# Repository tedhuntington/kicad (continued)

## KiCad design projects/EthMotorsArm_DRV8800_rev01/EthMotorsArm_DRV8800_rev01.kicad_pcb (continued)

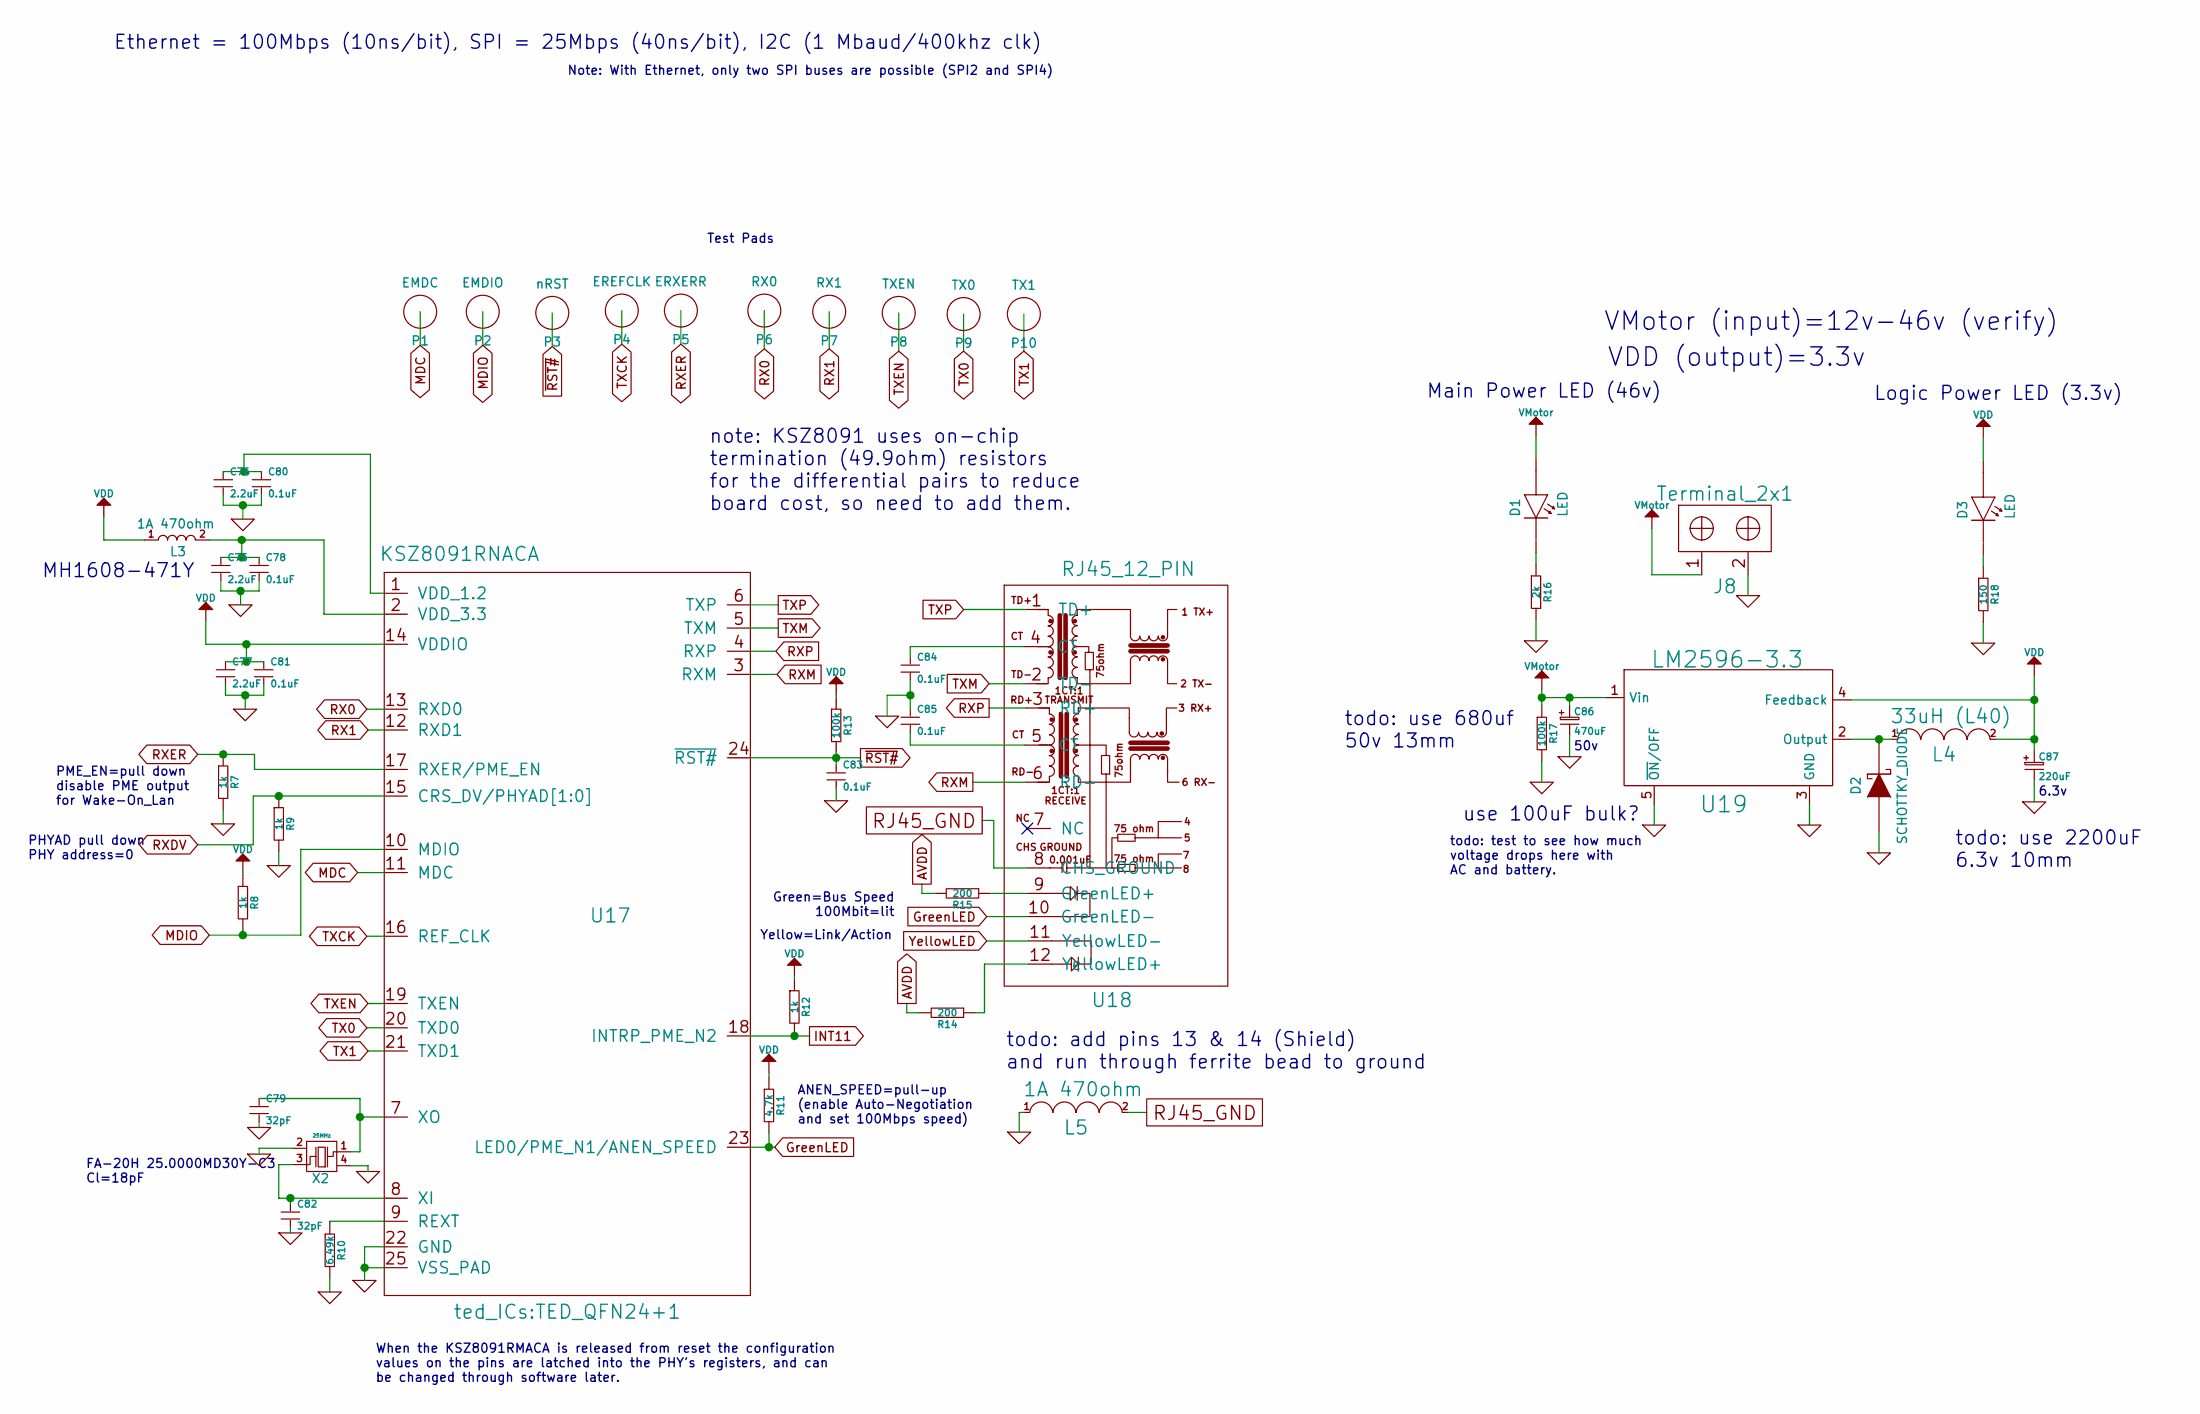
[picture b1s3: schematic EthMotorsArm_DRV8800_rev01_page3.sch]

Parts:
C75, C76, C77: 2.2uF; TED_SM0603_C
C78, C80, C81, C83, C84, C85: 0.1uF; TED_SM0603_C
C79, C82: 32pF; TED_SM0603_C
C86: 470uF; CP_Radial_D12.5mm_P5.00mm
C87: 220uF; TED_c_elec_radial_10mm
D1, D3: LED; TED_SM1206_LED
D2: SCHOTTKY_DIODE; TED_DO-214AC
J8: Terminal_2x1; TED_TERMINAL_5mm_2x1
L3, L5: 1A 470ohm; TED_SM0603_R
L4: 33uH (L40); INDUCTOR_12x12_SMD
P1: EMDC; TED_TEST_PAD
P2: EMDIO; TED_TEST_PAD
P3: nRST; TED_TEST_PAD
P4: EREFCLK; TED_TEST_PAD
P5: ERXERR; TED_TEST_PAD
P6: RX0; TED_TEST_PAD
P7: RX1; TED_TEST_PAD
P8: TXEN; TED_TEST_PAD
P9: TX0; TED_TEST_PAD
P10: TX1; TED_TEST_PAD
R7, R8, R9, R12: 1k; TED_SM0603_R
R10: 6.49k; TED_SM0603_R
R11: 4.7k; TED_SM0603_R
R13, R17: 100k; TED_SM0603_R
R14, R15: 200; TED_SM0603_R
R16: 2k; TED_SM0603_R
R18: 150; TED_SM0603_R
U17: KSZ8091RNACA; TED_QFN24+1
U18: RJ45_12_PIN; TED_RJ45_12pin
U19: LM2596-3.3; TED_TO263
X2: 25MHz; TED_crystal_FA-20H

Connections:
AVDD: R14.2, R15.2
GND: C75.2, C76.2, C77.2, C78.2, C79.2, C80.2, C81.2, C82.2, C83.2, C84.2, C85.1, C86.2, C87.2, D2.2 (A), J8.2, L5.1, R7.2, R9.2, R10.2, R16.2, R17.2, R18.2, U17.22 (GND), U17.25 (VSS_PAD), U19.3 (GND), U19.5 (~ON~/OFF), X2.2, X2.4; also elsewhere on the board
GreenLED: R11.2, U17.23 (LED0/PME_N1/ANEN_SPEED), U18.10 (GreenLED-)
INT11: R12.2, U17.18 (INTRP_PME_N2); also elsewhere on the board
MDC: P1.1, U17.11 (MDC); also elsewhere on the board
MDIO: P2.1, R8.2, U17.10 (MDIO); also elsewhere on the board
unnamed: C75.1, C78.1, L3.2, U17.2 (VDD_3.3)
unnamed: C76.1, C80.1, U17.1 (VDD_1.2)
unnamed: C79.1, U17.7 (XO), X2.1
unnamed: C82.1, U17.8 (XI), X2.3
unnamed: C84.1, U18.4 (CT)
unnamed: C85.2, U18.5 (CT)
unnamed: D1.2 (K), R16.1
unnamed: D2.1 (K), L4.1, U19.2 (Output)
unnamed: D3.2 (K), R18.1
unnamed: R10.1, U17.9 (REXT)
unnamed: R14.1, U18.12 (YellowLED+)
unnamed: R15.1, U18.9 (GreenLED+)
RJ45_GND: L5.2, U18.8 (CHS_GROUND)
RX0: P6.1, U17.13 (RXD0); also elsewhere on the board
RX1: P7.1, U17.12 (RXD1); also elsewhere on the board
RXDV: R9.1, U17.15 (CRS_DV/PHYAD[1:0]); also elsewhere on the board
RXER: P5.1, R7.1, U17.17 (RXER/PME_EN); also elsewhere on the board
RXM: U17.3 (RXM), U18.6 (RD-)
RXP: U17.4 (RXP), U18.3 (RD+)
TX0: P9.1, U17.20 (TXD0); also elsewhere on the board
TX1: P10.1, U17.21 (TXD1); also elsewhere on the board
TXCK: P4.1, U17.16 (REF_CLK); also elsewhere on the board
TXEN: P8.1, U17.19 (TXEN); also elsewhere on the board
TXM: U17.5 (TXM), U18.2 (TD-)
TXP: U17.6 (TXP), U18.1 (TD+)
VDD: C77.1, C81.1, C87.1, D3.1 (A), L3.1, L4.2, R8.1, R11.1, R12.1, R13.1, U17.14 (VDDIO), U19.4 (Feedback); also elsewhere on the board
VMotor: C86.1, D1.1 (A), J8.1, R17.1, U19.1 (Vin); also elsewhere on the board
YellowLED: U18.11 (YellowLED-); also elsewhere on the board
~RST#~: C83.1, P3.1, R13.2, U17.24 (~RST#~)

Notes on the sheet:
Ethernet = 100Mbps (10ns/bit), SPI = 25Mbps (40ns/bit), I2C (1 Mbaud/400khz clk)
Note: With Ethernet, only two SPI buses are possible (SPI2 and SPI4)
Yellow=Link/Action
Green=Bus Speed 100Mbit=lit
VDD (output)=3.3v
VMotor (input)=12v-46v (verify)
50v
6.3v
Main Power LED (46v)
Logic Power LED (3.3v)
note: KSZ8091 uses on-chip termination (49.9ohm) resistors for the differential pairs to reduce board cost, so need to add them.
MH1608-471Y
FA-20H 25.0000MD30Y-C3 Cl=18pF
ANEN_SPEED=pull-up (enable Auto-Negotiation and set 100Mbps speed)
PME_EN=pull down disable PME output for Wake-On_Lan
PHYAD pull down PHY address=0
When the KSZ8091RMACA is released from reset the configuration values on the pins are latched into the PHY's registers, and can be changed through software later.
Test Pads
todo: add pins 13 & 14 (Shield) and run through ferrite bead to ground
todo: test to see how much voltage drops here with AC and battery.
use 100uF bulk?
todo: use 680uf 50v 13mm
todo: use 2200uF 6.3v 10mm

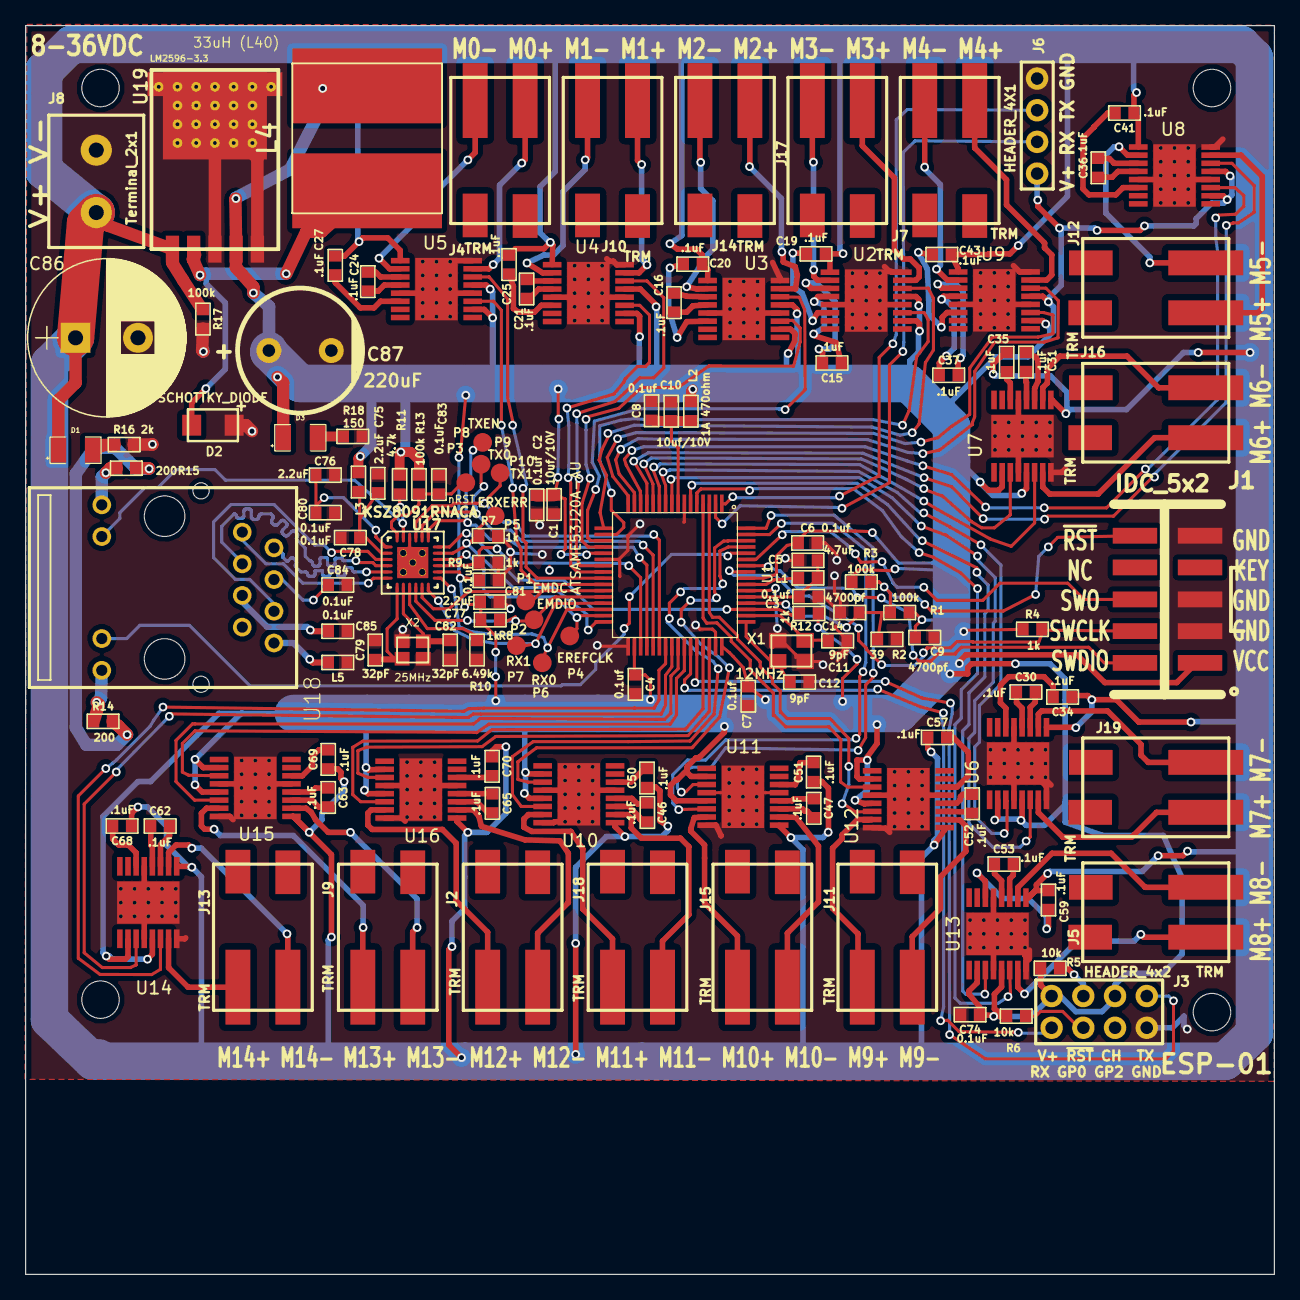
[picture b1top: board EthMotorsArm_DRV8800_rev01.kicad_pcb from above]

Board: 2 copper layers, 100.0 x 100.0 mm, 137 parts (0 on the bottom side), 155 nets.

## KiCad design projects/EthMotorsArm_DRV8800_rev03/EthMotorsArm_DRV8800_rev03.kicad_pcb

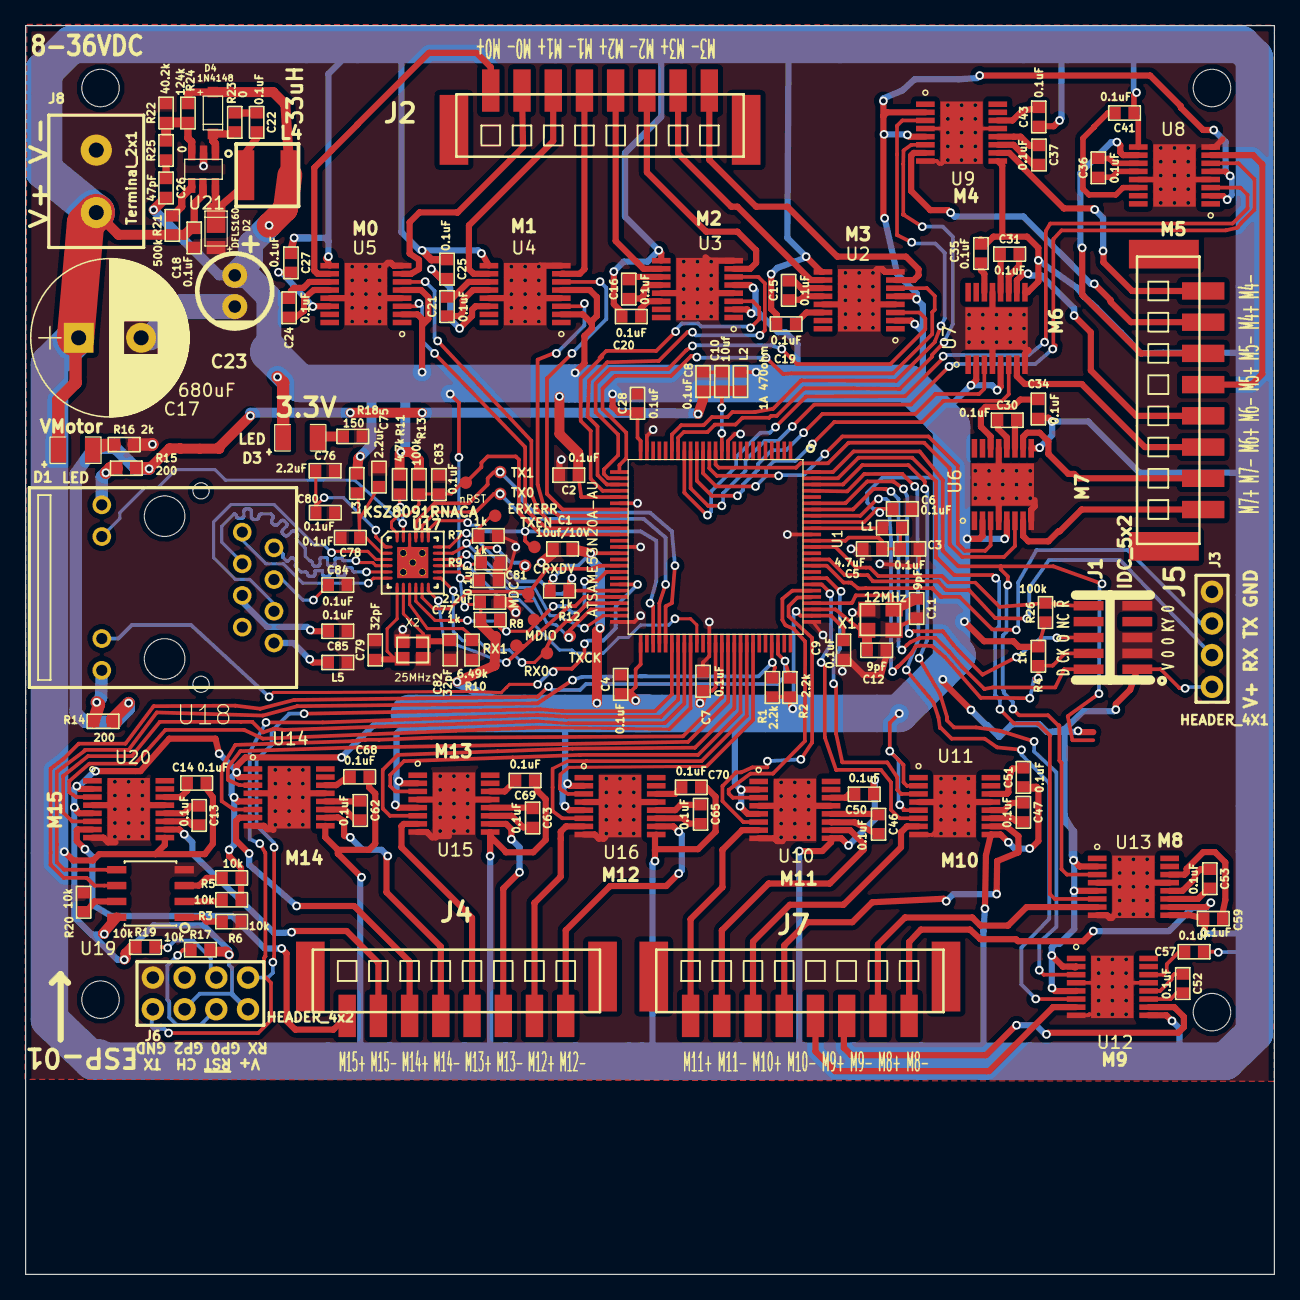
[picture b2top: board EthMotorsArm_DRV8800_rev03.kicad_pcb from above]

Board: 2 copper layers, 100.0 x 100.0 mm, 142 parts (0 on the bottom side), 172 nets.

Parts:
C1: 10uf/10V; TED_SM1608_0603_C
C2, C3, C4, C6, C7, C8, C9, C13, C14, C15, C16, C18, C19, C20, C21, C22, C24, C25, C27, C28, C30, C31, C34, C35, C36, C37, C41, C43, C46, C47, C50, C51, C52, C53, C57, C59, C62, C63, C65, C68, C69, C70, C78, C80, C81, C83, C84, C85: 0.1uF; TED_SM1608_0603_C
C5: 4.7uF; TED_SM1608_0603_C
C10: 10uf; TED_SM1608_0603_C
C11, C12: 9pF; TED_SM1608_0603_C
C17: 680uF; CP_Radial_D12.5mm_P5.00mm
C23: 220uF; TED_c_elec_radial_6.3mm
C26: 47pF; TED_SM1608_0603_C
C75, C76, C77: 2.2uF; TED_SM1608_0603_C
C79, C82: 32pF; TED_SM1608_0603_C
D1, D3: LED; TED_SM1206_LED
D2: DFLS160; TED_PowerDI123
D4: 1N4148; TED_SOD-123
H1, H2, H3, H4: HOLE; TED_Hole_3mm
J1: IDC_5x2; TED_IDC_5x2_1.27pitch_SMD_nm
J2, J4, J5, J7: Terminal_8x1_rev; TED_Terminal_8x1_1814760
J3: HEADER_4X1; TED_HEADER_4x1
J6: HEADER_4x2; TED_HEADER_4x2
J8: Terminal_2x1; TED_TERMINAL_5mm_2x1
L1, L2, L3, L5: 1A 470ohm; TED_SM0603_R
L4: 33uH; INDUCTOR_5x5_SMD
P1: MDC; TED_TEST_PAD
P2: MDIO; TED_TEST_PAD
P3: nRST; TED_TEST_PAD
P4: TXCK; TED_TEST_PAD
P5: ERXERR; TED_TEST_PAD
P6: RX0; TED_TEST_PAD
P7: RX1; TED_TEST_PAD
P8: TXEN; TED_TEST_PAD
P9: TX0; TED_TEST_PAD
P10: TX1; TED_TEST_PAD
P11: CRXDV; TED_TEST_PAD
R1, R2: 2.2k; TED_SM0603_R
R3, R5, R6, R17, R19, R20: 10k; TED_SM0603_R
R4, R7, R8, R9, R12: 1k; TED_SM0603_R
R10: 6.49k; TED_SM0603_R
R11: 4.7k; TED_SM0603_R
R13, R26: 100k; TED_SM0603_R
R14, R15: 200; TED_SM0603_R
R16: 2k; TED_SM0603_R
R18: 150; TED_SM0603_R
R21: 500k; TED_SM0603_R
R22: 40.2k; TED_SM0603_R
R23, R25: 0; TED_SM0603_R
R24: 124k; TED_SM0603_R
U1: ATSAME53N20A-AU; TED_TQFP100
U2, U3, U4, U5, U6, U7, U8, U9, U10, U11, U12, U13, U14, U15, U16, U20: DRV8800_PWP; TSSOP_16+1H
U17: KSZ8091RNACA; TED_QFN24+1
U18: RJ45_12_PIN; TED_RJ45_12pin
U19: AT24MAC402; SOIC-8
U21: MP2456; TSOT23-6
X1: 12MHz; crystal_3.2_2.5
X2: 25MHz; TED_crystal_FA-20H

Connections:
CRXDV: P11.1, R9.1, U1.60, U17.15
ESP_RX_SAM_TX: J6.8, U1.56
ESP_TX_SAM_RX: J6.1, U1.57
GND: C1.2, C2.2, C3.2, C4.2, C5.2, C6.2, C7.2, C8.2, C9.2, C10.2, C11.2, C12.2, C17.2, C18.2, C23.2, C28.2, C75.2, C76.2, C77.2, C78.2, C79.2, C80.2, C81.2, C82.2, C83.2, C84.2, C85.1, D2.1, J1.3, J1.5, J1.9, J3.4, J6.2, J8.2, L5.1, R3.2, R7.2, R9.2, R10.2, R16.2, R18.2, R20.1, R22.2, U1.11, U1.24, U1.31, U1.38, U1.50, U1.62, U1.76, U1.90, U2.4, U2.8, U2.13, U2.17, U3.4, U3.8, U3.13, U3.17, U4.4, U4.8, U4.13, U4.17, U5.4, U5.8, U5.13, U5.17, U6.4, U6.8, U6.13, U6.17, U7.4, U7.8, U7.13, U7.17, U8.4, U8.8, U8.13, U8.17, U9.4, U9.8, U9.13, U9.17, U10.4, U10.8, U10.13, U10.17, U11.4, U11.8, U11.13, U11.17, U12.4, U12.8, U12.13, U12.17, U13.4, U13.8, U13.13, U13.17, U14.4, U14.8, U14.13, U14.17, U15.4, U15.8, U15.13, U15.17, U16.4, U16.8, U16.13, U16.17, U17.22, U17.25, U19.4, U20.4, U20.8, U20.13, U20.17, U21.2, X1.2, X1.4, X2.2, X2.4
GreenLED: R11.2, U17.23, U18.10
INT15: R12.2, U1.45, U17.18
M0+: J2.2, U5.7
M0-: J2.1, U5.10
M0_1_PB12: U1.34, U5.6
M0_2_PB13: U1.35, U5.3
M1+: J2.4, U4.7
M1-: J2.3, U4.10
M1_1_PB10: U1.32, U4.6
M1_2_PB11: U1.33, U4.3
M2+: J2.6, U3.7
M2-: J2.5, U3.10
M2_1_PA10: U1.28, U3.6
M2_2_PA11: U1.29, U3.3
M3+: J2.8, U2.7
M3-: J2.7, U2.10
M3_1_PA08: U1.26, U2.6
M3_2_PA09: U1.27, U2.3
M4+: J5.2, U9.7
M4-: J5.1, U9.10
M4_1_PA06: U1.19, U9.6
M4_2_PA07: U1.20, U9.3
M5+: J5.4, U8.7
M5-: J5.3, U8.10
M5_1_PA04: U1.17, U8.6
M5_2_PA05: U1.18, U8.3
M6+: J5.6, U7.7
M6-: J5.5, U7.10
M6_1_PB08: U1.15, U7.6
M6_2_PB09: U1.16, U7.3
M7+: J5.8, U6.7
M7-: J5.7, U6.10
M7_1_PB06: U1.13, U6.6
M7_2_PB07: U1.14, U6.3
M8+: J7.2, U13.7
M8-: J7.1, U13.10
M8_1_PB02: U1.99, U13.6
M8_2_PB03: U1.100, U13.3
M9+: J7.4, U12.7
M9-: J7.3, U12.10
M9_1_PB00: U1.97, U12.6
M9_2_PB01: U1.98, U12.3
M10+: J7.6, U11.7
M10-: J7.5, U11.10
M10_1_PC24: U1.82, U11.6
M10_2_PC25: U1.83, U11.3
M11+: J7.8, U10.7
M11-: J7.7, U10.10
M11_1_PB24: U1.80, U10.6
M11_2_PB25: U1.81, U10.3
M12+: J4.2, U16.7
M12-: J4.1, U16.10
M12_1_PA24: U1.68, U16.6
M12_2_PA25: U1.69, U16.3
M13+: J4.4, U15.7
M13-: J4.3, U15.10
M13_1_PA22: U1.66, U15.6
M13_2_PA23: U1.67, U15.3
M14+: J4.6, U14.7
M14-: J4.5, U14.10
M14_1_PA20: U1.64, U14.6
M14_2_PA21: U1.65, U14.3
M15+: J4.8, U20.7
M15-: J4.7, U20.10
M15_1_PB20: U1.58, U20.6
M15_2_PB21: U1.59, U20.3
MDC: P1.1, U1.41, U17.11
MDIO: P2.1, R8.2, U1.42, U17.10
unnamed: C13.1, U20.12
unnamed: C13.2, U20.11
unnamed: C14.2, U20.14
unnamed: C15.1, U2.12
unnamed: C15.2, U2.11
unnamed: C16.1, U3.12
unnamed: C16.2, U3.11
unnamed: C19.2, U2.14
unnamed: C20.2, U3.14
unnamed: C21.1, U4.12
unnamed: C21.2, U4.11
unnamed: C22.1, R23.2
unnamed: C22.2, D2.2, L4.1, U21.6
unnamed: C24.1, U5.12
unnamed: C24.2, U5.11
unnamed: C25.2, U4.14
unnamed: C26.1, R25.1
unnamed: C27.2, U5.14
unnamed: C30.1, U6.12
unnamed: C30.2, U6.11
unnamed: C31.1, U7.12
unnamed: C31.2, U7.11
unnamed: C34.2, U6.14
unnamed: C35.2, U7.14
unnamed: C36.1, U8.12
unnamed: C36.2, U8.11
unnamed: C37.1, U9.12
unnamed: C37.2, U9.11
unnamed: C41.2, U8.14
unnamed: C43.2, U9.14
unnamed: C46.1, U10.12
unnamed: C46.2, U10.11
unnamed: C47.1, U11.12
unnamed: C47.2, U11.11
unnamed: C50.2, U10.14
unnamed: C51.2, U11.14
unnamed: C52.1, U12.12
unnamed: C52.2, U12.11
unnamed: C53.1, U13.12
unnamed: C53.2, U13.11
unnamed: C57.2, U12.14
unnamed: C59.2, U13.14
unnamed: C62.1, U14.12
unnamed: C62.2, U14.11
unnamed: C63.1, U15.12
unnamed: C63.2, U15.11
unnamed: C65.1, U16.12
unnamed: C65.2, U16.11
unnamed: C68.2, U14.14
unnamed: C69.2, U15.14
unnamed: C70.2, U16.14
unnamed: C75.1, C78.1, L3.2, U17.2
unnamed: C76.1, C80.1, U17.1
unnamed: C79.1, U17.7, X2.1
unnamed: C82.1, U17.8, X2.3
unnamed: C84.1, U18.4
unnamed: C85.2, U18.5
unnamed: D1.2, R16.1
unnamed: D3.2, R18.1
unnamed: D4.2, R23.1, U21.1
unnamed: J6.5, R17.1
unnamed: J6.6, R19.2
unnamed: R3.1, U19.1
unnamed: R5.1, U19.3
unnamed: R6.1, U19.2
unnamed: R10.1, U17.9
unnamed: R14.1, U18.12
unnamed: R15.1, U18.9
unnamed: R20.2, U19.7
unnamed: R21.2, U21.4
unnamed: R22.1, R24.2, R25.2, U21.3
RJ45_GND: L5.2, U18.8
RX0: P6.1, U1.47, U17.13
RX1: P7.1, U1.46, U17.12
RXER: P5.1, R7.1, U1.49, U17.17
RXM: U17.3, U18.6
RXP: U17.4, U18.3
SCL: R2.1, U1.73, U19.6
SDA: R1.1, U1.72, U19.5
SWCLK: J1.4, R4.2, U1.93
SWDIO: J1.2, U1.94
SWO: J1.6, U1.95
TX0: P9.1, U1.54, U17.20
TX1: P10.1, U1.55, U17.21
TXCK: P4.1, U1.48, U17.16
TXEN: P8.1, U1.53, U17.19
TXM: U17.5, U18.2
TXP: U17.6, U18.1
USART1RX: J3.2, U1.86
USART1TX: J3.3, U1.85
VDDANA: C8.1, C10.1, L2.2, R14.2, R15.2, U1.12
VDDIO: C1.1, C2.1, C4.1, C6.1, C7.1, C9.1, C23.1, C26.2, C28.1, C77.1, C81.1, D3.1, D4.1, J1.1, J3.1, J6.3, J6.7, L2.1, L3.1, L4.2, R1.2, R2.2, R4.1, R5.2, R6.2, R8.1, R11.1, R12.1, R13.1, R17.2, R19.1, R24.1, R26.1, U1.25, U1.30, U1.39, U1.51, U1.63, U1.77, U1.92, U2.2, U2.5, U3.2, U3.5, U4.2, U4.5, U5.2, U5.5, U6.2, U6.5, U7.2, U7.5, U8.2, U8.5, U9.2, U9.5, U10.2, U10.5, U11.2, U11.5, U12.2, U12.5, U13.2, U13.5, U14.2, U14.5, U15.2, U15.5, U16.2, U16.5, U17.14, U19.8, U20.2, U20.5
VDD_MCU_VDDCORE: C3.1, C5.1, L1.2, U1.89
VDD_MCU_VSW: L1.1, U1.91
VMotor: C14.1, C17.1, C18.1, C19.1, C20.1, C25.1, C27.1, C34.1, C35.1, C41.1, C43.1, C50.1, C51.1, C57.1, C59.1, C68.1, C69.1, C70.1, D1.1, J8.1, R21.1, U2.9, U3.9, U4.9, U5.9, U6.9, U7.9, U8.9, U9.9, U10.9, U11.9, U12.9, U13.9, U14.9, U15.9, U16.9, U20.9, U21.5
XIN: C12.1, U1.78, X1.3
XOUT: C11.1, U1.79, X1.1
YellowLED: U1.44, U18.11
~RESET~: J1.10, R26.2, U1.88
~RST#~: C83.1, P3.1, R13.2, U1.36, U17.24

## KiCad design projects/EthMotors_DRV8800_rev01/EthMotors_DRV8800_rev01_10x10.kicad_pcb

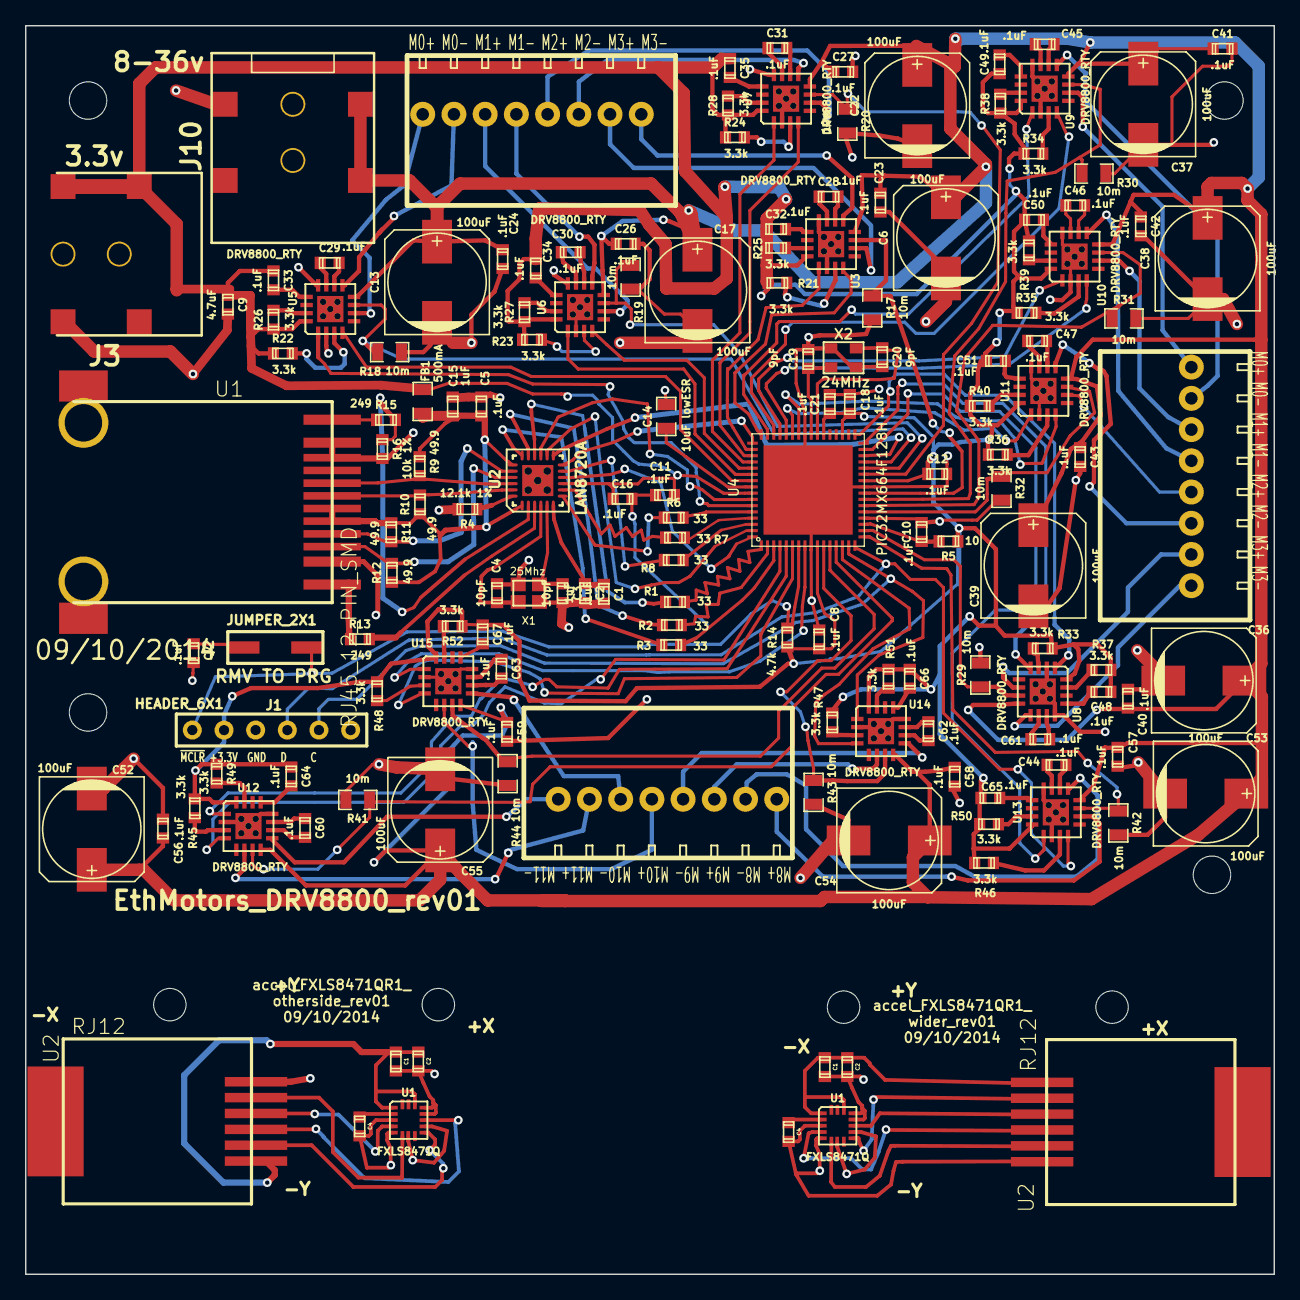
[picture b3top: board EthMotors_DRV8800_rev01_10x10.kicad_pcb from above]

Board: 2 copper layers, 100.0 x 100.0 mm, 161 parts (0 on the bottom side), 164 nets.

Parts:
C1, C1#2: 1uF; TED_SM0603
C1#3, C5, C7, C8, C10, C11, C12, C16, C18, C21, C23, C24, C26, C27, C28, C29, C30, C31, C32, C33, C34, C35, C40, C41, C42, C43, C44, C45, C46, C47, C48, C49, C50, C51, C56, C57, C58, C59, C60, C61, C62, C63, C64, C65, C66, C67: .1uF; TED_SM0603_C
C2, C2#2, C4, C4#2: .1uF; TED_SM0603
C2#3, C15: 1uF; TED_SM0603_C
C3, C4#3: 10pF; TED_SM0603_C
C6, C13, C17, C22, C36, C37, C38, C39, C52, C53, C54, C55: 100uF; TED_c_elec_8x10
C9: 4.7uF; TED_SM0603_C
C14: 10uF lowESR; TED_SM0805_C
C19, C20: 9pF; TED_SM0603_C
FB1: 500mA; TED_SM0805_R
H1, H1#2, H2, H2#2: HOLE; TED_Hole_2_6mm
H1#3, H2#3, H3, H4: HOLE; TED_Hole_3mm
J1: HEADER_6X1; TED_HEADER_6x1
J2: JUMPER_2X1; TED_HEADER_2x1_SMT
J3, J10: Logic DC_2.1MM; TED_DC_2.1mm_SMT
J4, J5, J7: TERMINAL_8X1; TED_TERMINAL_SPRING_2.54MM_8PIN_1989803
R1, R2, R3, R6, R7, R8: 33; TED_SM0603_R
R4: 12.1k 1%; TED_SM0603_R
R5: 10; TED_SM0603_R
R9, R10, R11, R12: 49.9; TED_SM0603_R
R13, R15: 249; TED_SM0603_R
R14: 4.7k; TED_SM0603_R
R16: 10k 1%; TED_SM0603_R
R17, R18, R19, R20, R29, R30, R31, R32, R41, R42, R43, R44: 10m; TED_SM0805_R
R21, R22, R23, R24, R25, R26, R27, R28, R33, R34, R35, R36, R37, R38, R39, R40, R45, R46, R47, R48, R49, R50, R51, R52: 3.3k; TED_SM0603_R
U1, U1#2: FXLS8471Q; TED_QFN16_3x5
U1#3: RJ45_12_PIN_SMD; TED_RJ45_12pin_SMD
U2, U2#2: RJ12; TED_RJ12_855135002
U2#3: LAN8720A; TED_QFN24
U3, U5, U6, U7, U8, U9, U10, U11, U12, U13, U14, U15: DRV8800_RTY; TED_QFN16+1
U4: PIC32MX664F128H; TED_QFN64+1
X1: 25Mhz; TED_crystal_FA-20H
X2: 24MHz; TED_crystal_TSX3225

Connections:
AVDD: C5.1, C15.1, FB1.2, R9.1, R10.1, R11.1, R12.1, U1#3.5, U1#3.6, U2#3.1, U2#3.19
ECRSDV: R8.2, U4.62
EMDC: U2#3.13, U4.30
EMDIO: U2#3.12, U4.49
EREFCLK: U2#3.14, U4.63
ERXD0: R7.2, U4.61
ERXD1: R6.2, U4.60
ERXERR: U2#3.10, U4.64
ETXD0: R2.2, U4.2
ETXD1: R3.2, U4.3
ETXEN: R1.2, U4.1
GND: C1.2, C1#2.2, C1#3.2, C2.2, C2#2.2, C2#3.2, C3.2, C4.2, C4#2.2, C4#3.1, C5.2, C6.2, C7.2, C8.2, C9.2, C10.2, C11.2, C12.2, C13.2, C14.2, C15.2, C16.2, C17.2, C18.2, C19.2, C20.2, C21.2, C22.2, C23.2, C24.2, C26.2, C27.2, C36.2, C37.2, C38.2, C39.2, C40.2, C41.2, C42.2, C43.2, C52.2, C53.2, C54.2, C55.2, C56.2, C57.2, C58.2, C59.2, J1.3, J3.2, J10.2, R4.2, R16.2, R17.2, R18.2, R19.2, R20.2, R29.2, R30.2, R31.2, R32.2, R41.2, R42.2, R43.2, R44.2, U1.3, U1.5, U1.7, U1.10, U1.12, U1.13, U1#2.3, U1#2.5, U1#2.7, U1#2.10, U1#2.12, U1#2.13, U1#3.2, U1#3.10, U1#3.11, U2.1, U2#2.1, U2#3.25, U3.2, U3.12, U3.17, U4.9, U4.20, U4.25, U4.41, U4.65, U5.2, U5.12, U5.17, U6.2, U6.12, U6.17, U7.2, U7.12, U7.17, U8.2, U8.12, U8.17, U9.2, U9.12, U9.17, U10.2, U10.12, U10.17, U11.2, U11.12, U11.17, U12.2, U12.12, U12.17, U13.2, U13.12, U13.17, U14.2, U14.12, U14.17, U15.2, U15.12, U15.17, X1.2, X1.4, X2.2, X2.4
GreenLED: R15.1, U1#3.12
INT1: U1.11, U1#2.11, U2.4, U2#2.4
INT2: U1.9, U1#2.9, U2.5, U2#2.5
M0+: J7.8, U5.6
M0-: J7.7, U5.9
M1+: J7.6, U6.6
M1-: J7.5, U6.9
M2+: J7.4, U7.6
M2-: J7.3, U7.9
M3+: J7.2, U3.6
M3-: J7.1, U3.9
M4+: J4.8, U9.6
M4-: J4.7, U9.9
M5+: J4.6, U10.6
M5-: J4.5, U10.9
M6+: J4.4, U11.6
M6-: J4.3, U11.9
M7+: J4.2, U8.6
M7-: J4.1, U8.9
M8+: J5.8, U13.6
M8-: J5.7, U13.9
M9+: J5.6, U14.6
M9-: J5.5, U14.9
M10+: J5.4, U15.6
M10-: J5.3, U15.9
M11+: J5.2, U12.6
M11-: J5.1, U12.9
unnamed: C4.1, C4#2.1, R8.1, U1.2, U1#2.2, U2#3.11
unnamed: R3.1, U2#3.18
unnamed: R2.1, U2#3.17
unnamed: R1.1, U2#3.16
unnamed: R4.1, U2#3.24
unnamed: R6.1, U2#3.7
unnamed: R7.1, U2#3.8
unnamed: C19.1, U4.40, X2.1
unnamed: C4#3.2, U2#3.4, X1.3
unnamed: C1#3.1, C2#3.1, U2#3.6
unnamed: C3.1, U2#3.5, X1.1
unnamed: C10.1, R5.2, U4.19
unnamed: C7.1, J2.1
unnamed: R13.2, U2#3.3
unnamed: R15.2, R16.1, U2#3.2
unnamed: C20.1, U4.39, X2.3
unnamed: C65.2, U13.13
unnamed: C61.1, U13.11
unnamed: C61.2, U13.10
unnamed: R50.2, U13.15
unnamed: R33.2, U8.3
unnamed: C62.1, U14.11
unnamed: C62.2, U14.10
unnamed: R46.2, U13.3
unnamed: C66.2, U14.13
unnamed: R40.2, U11.15
unnamed: C51.2, U11.13
unnamed: C47.1, U11.11
unnamed: C47.2, U11.10
unnamed: C44.2, U8.10
unnamed: C44.1, U8.11
unnamed: R37.2, U8.15
unnamed: C48.2, U8.13
unnamed: R36.2, U11.3
unnamed: C64.2, U12.13
unnamed: R49.2, U12.15
unnamed: C60.1, U12.11
unnamed: C60.2, U12.10
unnamed: R45.2, U12.3
unnamed: R47.2, U14.3
unnamed: R51.2, U14.15
unnamed: C67.2, U15.13
unnamed: R48.2, U15.3
unnamed: C63.1, U15.11
unnamed: C63.2, U15.10
unnamed: R52.2, U15.15
unnamed: R23.2, U6.3
unnamed: R27.2, U6.15
unnamed: C30.1, U6.11
unnamed: C30.2, U6.10
unnamed: C34.2, U6.13
unnamed: C35.2, U7.13
unnamed: R28.2, U7.15
unnamed: C31.2, U7.10
unnamed: C31.1, U7.11
unnamed: C33.2, U5.13
unnamed: C29.1, U5.11
unnamed: C29.2, U5.10
unnamed: R26.2, U5.15
unnamed: R22.2, U5.3
unnamed: R34.2, U9.3
unnamed: C46.1, U10.11
unnamed: C49.2, U9.13
unnamed: R38.2, U9.15
unnamed: R35.2, U10.3
unnamed: C46.2, U10.10
unnamed: R39.2, U10.15
unnamed: C50.2, U10.13
unnamed: C28.1, U3.11
unnamed: C28.2, U3.10
unnamed: C32.2, U3.13
unnamed: R25.2, U3.15
unnamed: R24.2, U7.3
unnamed: C45.2, U9.10
unnamed: C45.1, U9.11
unnamed: R21.2, U3.3
PGEC1_RB1: J1.5, U4.15, U14.1
PGED1_RB0: J1.4, U4.16, U13.4
RB2: U4.14, U14.4
RB3: R41.1, U4.13, U12.7
RB4: R44.1, U4.12, U15.7
RB5: R43.1, U4.11, U14.7
RB6: R42.1, U4.17, U13.7
RB7: R29.1, U4.18, U8.7
RB8: R32.1, U4.21, U11.7
RB9: R31.1, U4.22, U10.7
RB10: R30.1, U4.23, U9.7
RB11: R17.1, U3.7, U4.24
RB12: R20.1, U4.27, U7.7
RB13: R19.1, U4.28, U6.7
RB14: R18.1, U4.29, U5.7
RC13: U4.47, U9.1
RC14: U3.4, U4.48
RD0: U4.46, U9.4
RD2: U3.1, U4.50
RD3: U4.51, U7.4
RD4: U4.52, U7.1
RD5: U4.53, U6.4
RD6: U4.54, U6.1
RD7: U4.55, U5.4
RD8: U4.42, U11.4
RD9: U4.43, U11.1
RD10: U4.44, U10.4
RD11: U4.45, U10.1
RF1: U4.59, U5.1
RF3: U4.33, U8.1
RF4: U4.31, U13.1
RF5: U4.32, U8.4
RG6: U4.4, U12.4
RG7: U4.5, U12.1
RG8: U4.6, U15.4
RG9: U4.8, U15.1
RXN: R9.2, U1#3.8, U2#3.22
RXP: R10.2, U1#3.7, U2#3.23
SCL: U1.4, U1#2.4, U2.3, U2#2.3
SDA: U1.6, U1#2.6, U2.2, U2#2.2
TXN: R11.2, U1#3.4, U2#3.20
TXP: R12.2, U1#3.3, U2#3.21
VCAP: C14.1, U4.56
VDD: C8.1, C9.1, C11.1, C12.1, C16.1, C18.1, C21.1, C32.1, C33.1, C34.1, C35.1, C48.1, C49.1, C50.1, C51.1, C64.1, C65.1, C66.1, C67.1, FB1.1, J1.2, J3.1, R5.1, R14.1, R21.1, R22.1, R23.1, R24.1, R25.1, R26.1, R27.1, R28.1, R33.1, R34.1, R35.1, R36.1, R37.1, R38.1, R39.1, R40.1, R45.1, R46.1, R47.1, R48.1, R49.1, R50.1, R51.1, R52.1, U2#3.9, U3.16, U4.10, U4.26, U4.35, U4.38, U4.57, U5.16, U6.16, U7.16, U8.16, U9.16, U10.16, U11.16, U12.16, U13.16, U14.16, U15.16
VMotor: C6.1, C13.1, C17.1, C22.1, C23.1, C24.1, C26.1, C27.1, C36.1, C37.1, C38.1, C39.1, C40.1, C41.1, C42.1, C43.1, C52.1, C53.1, C54.1, C55.1, C56.1, C57.1, C58.1, C59.1, J10.1, U3.8, U5.8, U6.8, U7.8, U8.8, U9.8, U10.8, U11.8, U12.8, U13.8, U14.8, U15.8
Vdd: C1.1, C1#2.1, C2.1, C2#2.1, U1.1, U1.14, U1#2.1, U1#2.14, U2.6, U2#2.6
YellowLED: R13.1, U1#3.1
nRST: U2#3.15, U4.58
~MCLR~: J1.1, J2.2, R14.2, U4.7

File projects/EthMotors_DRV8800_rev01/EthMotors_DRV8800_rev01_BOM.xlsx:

/home/ted/kicad/projects/EthMotors_DRV8800_rev01/EthMotors_DRV8800_rev01.sch
Sun 12 Oct 2014 08:54:45 PM PDT
eeschema (2013-08-24 BZR 4298)-stable
Component Count:147
Ref | Qnty | Value | Part | Part# | Unit Cost | Total Cost | Major Distributor | Minor Distributor
C11, C21, C12, C8, C16, C5, C18, C10, C1, C7, C29, C33, C24, C30, C34, C26, C31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 | 46 | .1uF | ted_capacitors/C(SMALL) | Vj0603V104ZXAPW1BC | 0.1 | 4.6 | Mouser
C13, C17, C22, C6, C37, C38, C39, C36, C53, C54, C55, C52, | 12 | 100uF | ted_capacitors/C_POL_SMALL | UWT1H101MNL 1GS | 0.44 | 5.28 | Mouser
C14, | 1 | 10uF (low ESR 1ohm) | ted_capacitors/C(SMALL) | LMK212F106ZG-T | 0.18 | 0.18 | Mouser
C19, C20, | 2 | 9pF | ted_capacitors/C(SMALL) | GRM1885C1H9R0DA01D | 0.1 | 0.2 | Digi-Key/Mouser
C2, C15, | 2 | 1uF | ted_capacitors/C(SMALL) | GRM188R61E105KA12D | 0.1 | 0.2 | Digi-Key
C4, C3, | 2 | 10pF | ted_capacitors/C(SMALL) | GRM1885C1H100FA01J | 0.12 | 0.24 | Mouser
C9, | 1 | 4.7uF | ted_capacitors/C(SMALL) | C0603C475K9PACTU | 0.13 | 0.13 | Mouser
FB1, | 1 | 500mA | ted_inductors/FERRITE_BEAD | MPZ2012S601A | 0.12 | 0.12 | Mouser
H1, H2, H4, H3, | 4 | HOLE | TED_holes/HOLE |  | 0 | 0
J1, | 1 | HEADER_6X1 | ted_connectors/HEADER_6X1 | 640456-6 | 0.27 | 0.27 | Mouser
J2, | 1 | JUMPER_2X1 | ted_connectors/JUMPER_2X1 | FCI 68000-102HLF | 0.19 | 0.19 | Digi-Key | AliExpress/Ebay
J3, J10, | 2 | Logic DC_2.1MM | ted_connectors/DC_2.1MM | Switchcraft RASM722X | 1.12 | 2.24 | Digi-Key/Mouser | AliExpress/Ebay
J7, J4, J5, | 3 | TERMINAL_8X1 | ted_connectors/TERMINAL_8X1 | 1814760 | 1.31 | 3.93 | Mouser
R12, R11, R10, R9, | 4 | 49.9 | ted_resistors/R_SMALL | ERJ-3EKF49R9V | 0.1 | 0.4 | Digi-Key
R14, | 1 | 4.7k | ted_resistors/R_SMALL | ERJ-3EKF4701V | 0.1 | 0.1 | Digi-Key
R15, R13, | 2 | 249 | ted_resistors/R_SMALL | ERJ-2RKF2490X | 0.1 | 0.2 | Digi-Key/Mouser
R16, | 1 | 10k 1% | ted_resistors/R_SMALL | ERJ-3EKF1001V | 0.1 | 0.1 | Digi-Key
R18, R19, R20, R17, R30, R31, R32, R29, R42, R43, R44, R41, | 12 | 10m | ted_resistors/R_SMALL | RL1220S-R10-F | 0.32 | 3.84 | Digi-Key
R26, R22, R27, R23, R28, R24, R25, R21, R38, R34, R39, R35, R40, R36, R37, R33,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 | 24 | 3.3k | ted_resistors/R_SMALL | ERJ-3EKF3301V | 0.1 | 2.4 | Digi-Key
R4, | 1 | 12.1k 1% | ted_resistors/R_SMALL | ERJ-6ENF1212V | 0.1 | 0.1 | Mouser
R5, | 1 | 10 | ted_resistors/R_SMALL | CRCW060310R0FKEA | 0.1 | 0.1 | Digi-Key/Mouser
R7, R6, R2, R1, R3, R8, | 6 | 33 | ted_resistors/R_SMALL | RC0603FR-0733RL | 0.1 | 0.6 | Digi-Key/Mouser
U1, | 1 | RJ45_12_PIN_SMD | ted_connectors/RJ45_12_PIN_SMD | HR961160C | 2.56 | 2.56 |  | AliExpress
U2, | 1 | LAN8720A | ted_ic/LAN8720A | LAN8720A | 1.49 | 1.49 | Digi-Key
U4, | 1 | PIC32MX664F128H | ted_ic/PIC32MX664F128H | PIC32MX664F128H-I/MR | 4.78 | 4.78 | MicrosoftDirect
U5, U6, U7, U3, U9, U10, U11, U8, U13, U14, U15, U12, | 12 | DRV8800_RTY | ted_ic/DRV8800_RTY | DRV8800RTYR | 2.38 | 28.56 | TI Store
X1, | 1 | 25Mhz | ted_crystals/CRYSTAL_W_2GND | FA-20H 25.0000MF20X-K3 | 0.73 | 0.73 | Mouser
X2, | 1 | 24MHz | ted_crystals/CRYSTAL_W_2GND | TSX-3225 24.0000MF20G-AC3 | 0.51 | 0.51 | Mouser
 |  |  |  |  |  | 64.05
